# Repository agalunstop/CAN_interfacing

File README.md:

# CAN_interfacing
Interfacing CAN MCP2515 module with arduino and Raspberry Pi

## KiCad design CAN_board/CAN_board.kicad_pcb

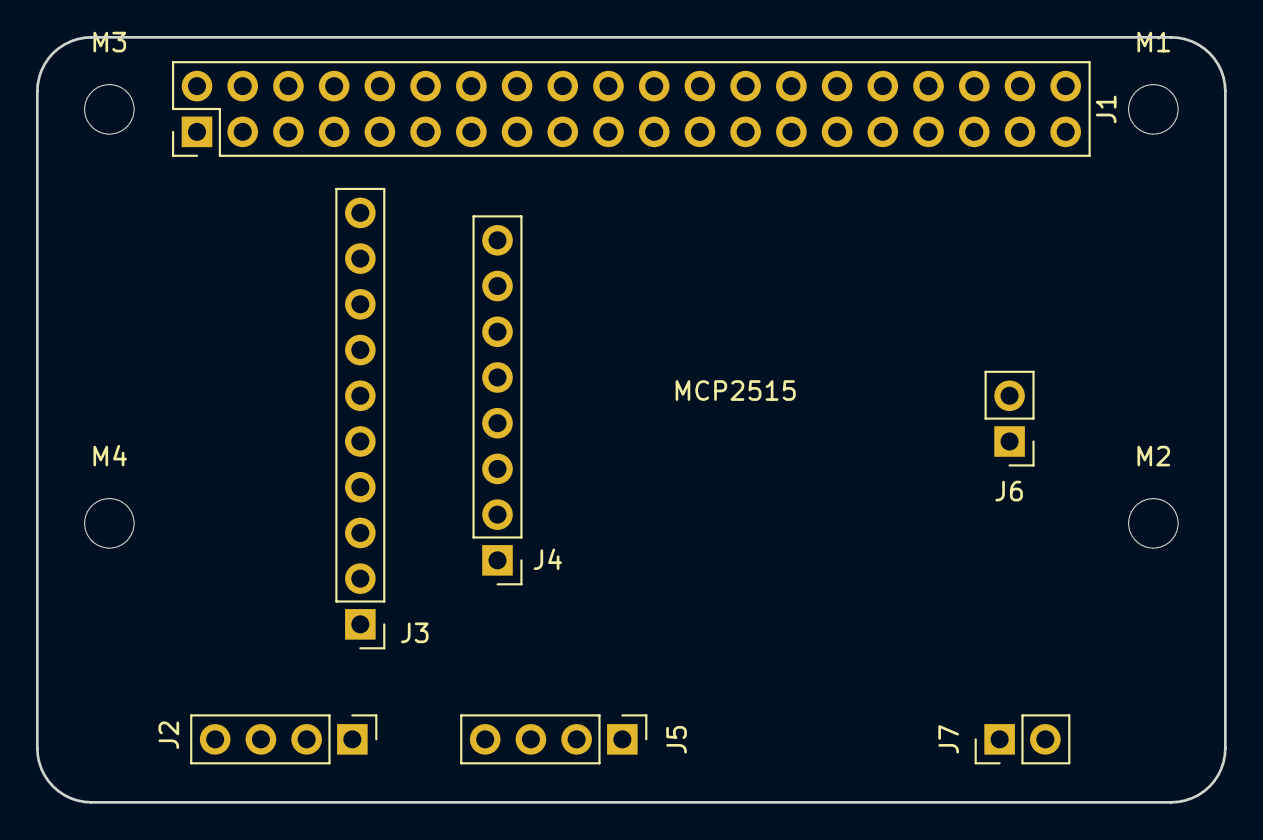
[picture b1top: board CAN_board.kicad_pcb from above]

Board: 2 copper layers, 66.0 x 42.5 mm, 11 parts (0 on the bottom side), 17 nets, no tracks yet.

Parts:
J1: Conn_02x20_Odd_Even_Rasbpi; PinHeader_2x20_P2.54mm_Vertical
J2: Sensor input; PinHeader_1x04_P2.54mm_Vertical
J3: ADS1115; PinHeader_1x10_P2.54mm_Vertical
J4: MCP2515; PinHeader_1x08_P2.54mm_Vertical
J5: Battery; PinHeader_1x04_P2.54mm_Vertical
J6, J7: Conn_01x02_Male; PinHeader_1x02_P2.54mm_Vertical
M1, M2, M3, M4: MountingHole_2.75mm; MountingHole_2.7mm

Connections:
/3V3: J1.1, J3.1, J4.1, J5.2
/5V: J1.2, J4.8, J5.1
/A0: J2.1, J3.7
/A1: J2.2, J3.8
/A2: J2.3, J3.9
/A3: J2.4, J3.10
/ALRT: J1.11, J3.6
/CANH: J6.1, J7.1
/CANL: J6.2, J7.2
/CS: J1.24, J4.3
/GND: J1.6, J1.9, J1.14, J1.20, J1.25, J1.30, J1.34, J1.39, J3.2, J3.5, J4.2, J5.3, J5.4
/INT: J1.22, J4.7
/MISO: J1.21, J4.4
/MOSI: J1.19, J4.5
/SCL: J1.5, J3.3
/SCLK: J1.23, J4.6
/SDA: J1.3, J3.4

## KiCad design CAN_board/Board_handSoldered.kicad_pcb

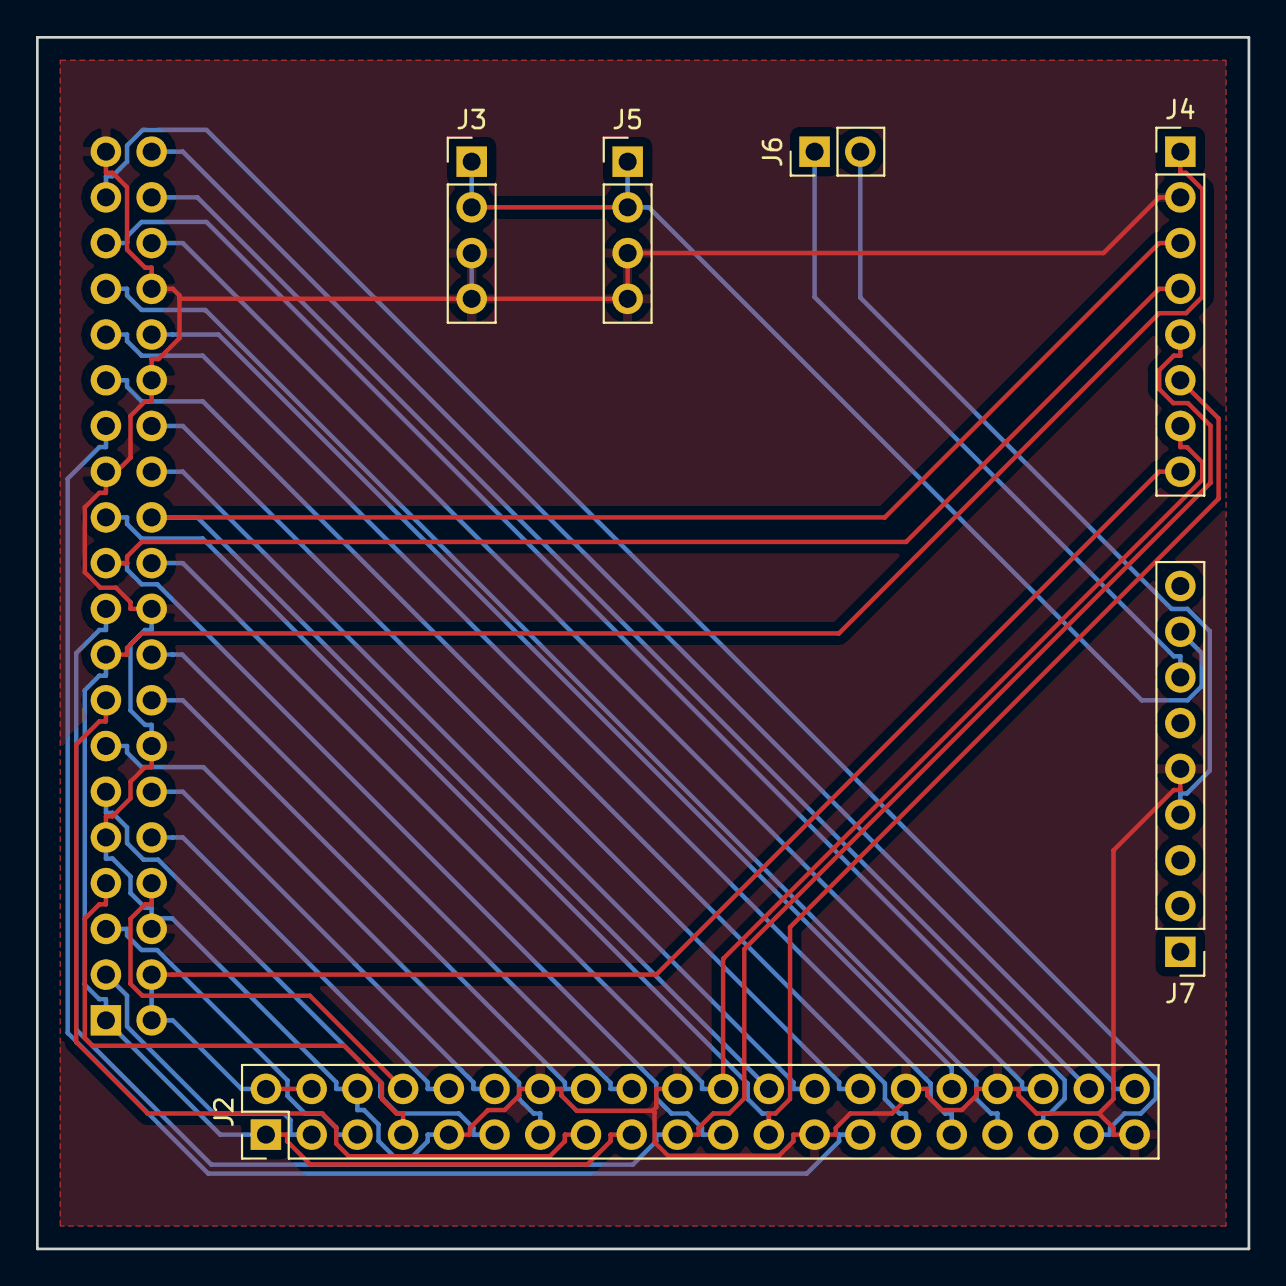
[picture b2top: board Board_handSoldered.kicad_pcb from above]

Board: 2 copper layers, 67.3 x 67.3 mm, 7 parts (1 on the bottom side), 34 nets.

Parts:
J1: Conn_02x20_Odd_Even_Rasbpi; PinHeader_2x20_P2.54mm_Vertical
J2: Conn_02x20_Odd_Even_extra; PinHeader_2x20_P2.54mm_Vertical
J3: Converter; PinHeader_1x04_P2.54mm_Vertical
J4: MCP2515; PinHeader_1x08_P2.54mm_Vertical
J5: Battery; PinHeader_1x04_P2.54mm_Vertical
J6: Conn_01x02_Male; PinHeader_1x02_P2.54mm_Vertical
J7: OBD_connector; PinHeader_1x09_P2.54mm_Vertical

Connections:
/3: J1.3, J2.3
/3V3: J1.1, J1.17, J2.1, J2.17, J4.1
/5: J1.5, J2.5
/5V: J1.2, J1.4, J2.2, J2.4, J4.8
/7: J1.7, J2.7
/8: J1.8, J2.8
/10: J1.10, J2.10
/11: J1.11, J2.11
/12: J1.12, J2.12
/12V: J3.1, J3.2, J5.1, J5.2, J7.8
/13: J1.13, J2.13
/15: J1.15, J2.15
/16: J1.16, J2.16
/18: J1.18, J2.18
/26: J1.26, J2.26
/27: J1.27, J2.27
/28: J1.28, J2.28
/29: J1.29, J2.29
/31: J1.31, J2.31
/32: J1.32, J2.32
/33: J1.33, J2.33
/35: J1.35, J2.35
/36: J1.36, J2.36
/37: J1.37, J2.37
/38: J1.38, J2.38
/40: J1.40, J2.40
/CANH: J6.1, J7.7
/CANL: J6.2, J7.4
/CS: J1.24, J2.24, J4.3
/GND: J1.6, J1.9, J1.14, J1.20, J1.25, J1.30, J1.34, J1.39, J2.6, J2.9, J2.14, J2.20, J2.25, J2.30, J2.34, J2.39, J3.3, J3.4, J4.2, J5.3, J5.4, J7.5
/INT: J1.22, J2.22, J4.7
/MISO: J1.21, J2.21, J4.4
/MOSI: J1.19, J2.19, J4.5
/SCLK: J1.23, J2.23, J4.6

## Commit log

2019-04-10 Components placed, routing to be done
